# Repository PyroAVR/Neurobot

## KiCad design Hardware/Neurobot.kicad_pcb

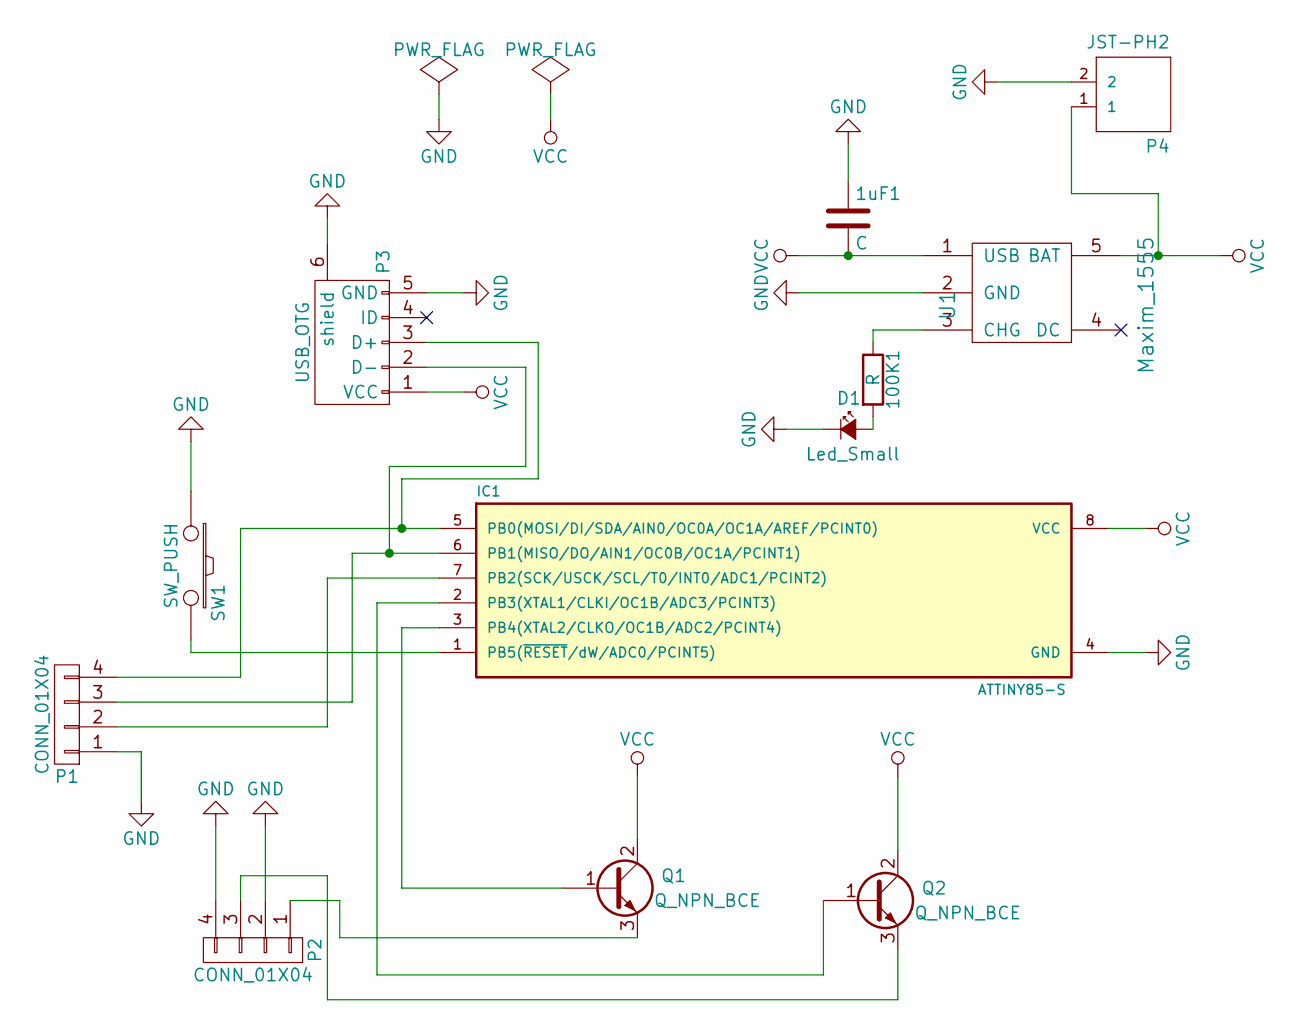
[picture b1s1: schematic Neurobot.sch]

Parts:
1uF1: C; C_0603_HandSoldering
100K1: R; R_0603_HandSoldering
D1: Led_Small; SMB_Standard
IC1: ATTINY85-S; SOIC-8_3.9x4.9mm_Pitch1.27mm
P1, P2: CONN_01X04; Pin_Header_Straight_1x04
P3: USB_OTG; USB_Mini-B
P4: JST-PH2; jst-ph-JST-PH2
Q1, Q2: Q_NPN_BCE; TO-92_Inline_Narrow_Oval
SW1: SW_PUSH; SW_SPST_EVPBF
U1: Maxim_1555; SOT-23-5

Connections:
GND: 1uF1.1, D1.1 (K), IC1.4 (GND), P1.1, P2.2, P2.4, P3.5 (GND), P3.6 (shield), P4.2, SW1.1, U1.2 (GND)
unnamed: 100K1.1, U1.3 (CHG)
unnamed: 100K1.2, D1.2 (A)
unnamed: IC1.1 (PB5(~RESET~/dW/ADC0/PCINT5)), SW1.2
unnamed: IC1.2 (PB3(XTAL1/CLKI/OC1B/ADC3/PCINT3)), Q2.1 (B)
unnamed: IC1.3 (PB4(XTAL2/CLKO/OC1B/ADC2/PCINT4)), Q1.1 (B)
unnamed: IC1.5 (PB0(MOSI/DI/SDA/AIN0/OC0A/OC1A/AREF/PCI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), P1.4, P3.3 (D+)
unnamed: IC1.6 (PB1(MISO/DO/AIN1/OC0B/OC1A/PCINT1)), P1.3, P3.2 (D-)
unnamed: IC1.7 (PB2(SCK/USCK/SCL/T0/INT0/ADC1/PCINT2)), P1.2
unnamed: P2.1, Q1.3 (E)
unnamed: P2.3, Q2.3 (E)
VCC: 1uF1.2, IC1.8 (VCC), P3.1 (VCC), P4.1, Q1.2 (C), Q2.2 (C), U1.1 (USB), U1.5 (BAT)

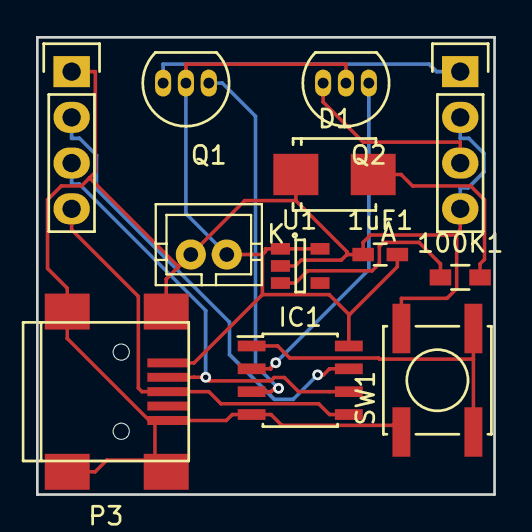
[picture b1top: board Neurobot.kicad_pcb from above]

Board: 2 copper layers, 25.4 x 25.4 mm, 12 parts (0 on the bottom side), 12 nets.

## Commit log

2015-11-24 Added Hardware components.
2015-12-04 Bill of Materials.
